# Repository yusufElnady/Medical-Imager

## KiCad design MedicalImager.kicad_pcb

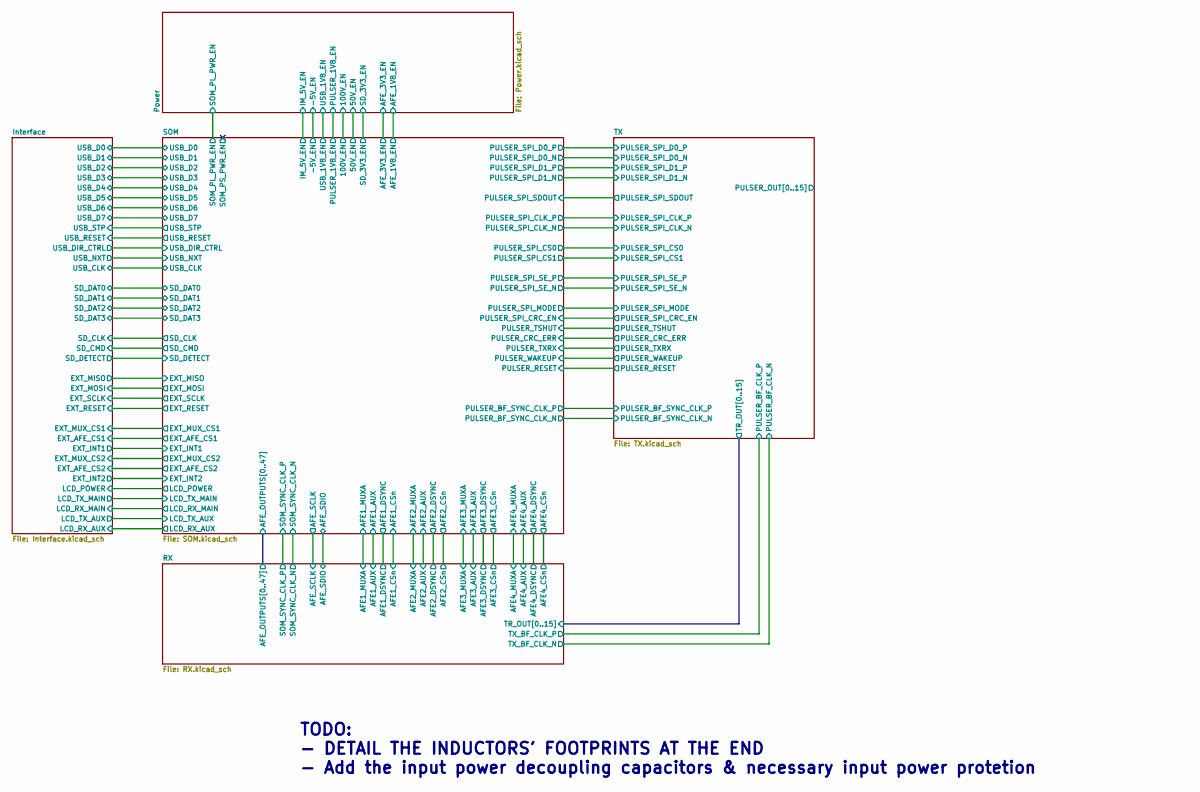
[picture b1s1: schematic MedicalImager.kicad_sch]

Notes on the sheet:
TODO: - DETAIL THE INDUCTORS' FOOTPRINTS AT THE END - Add the input power decoupling capacitors & necessary input power protetion

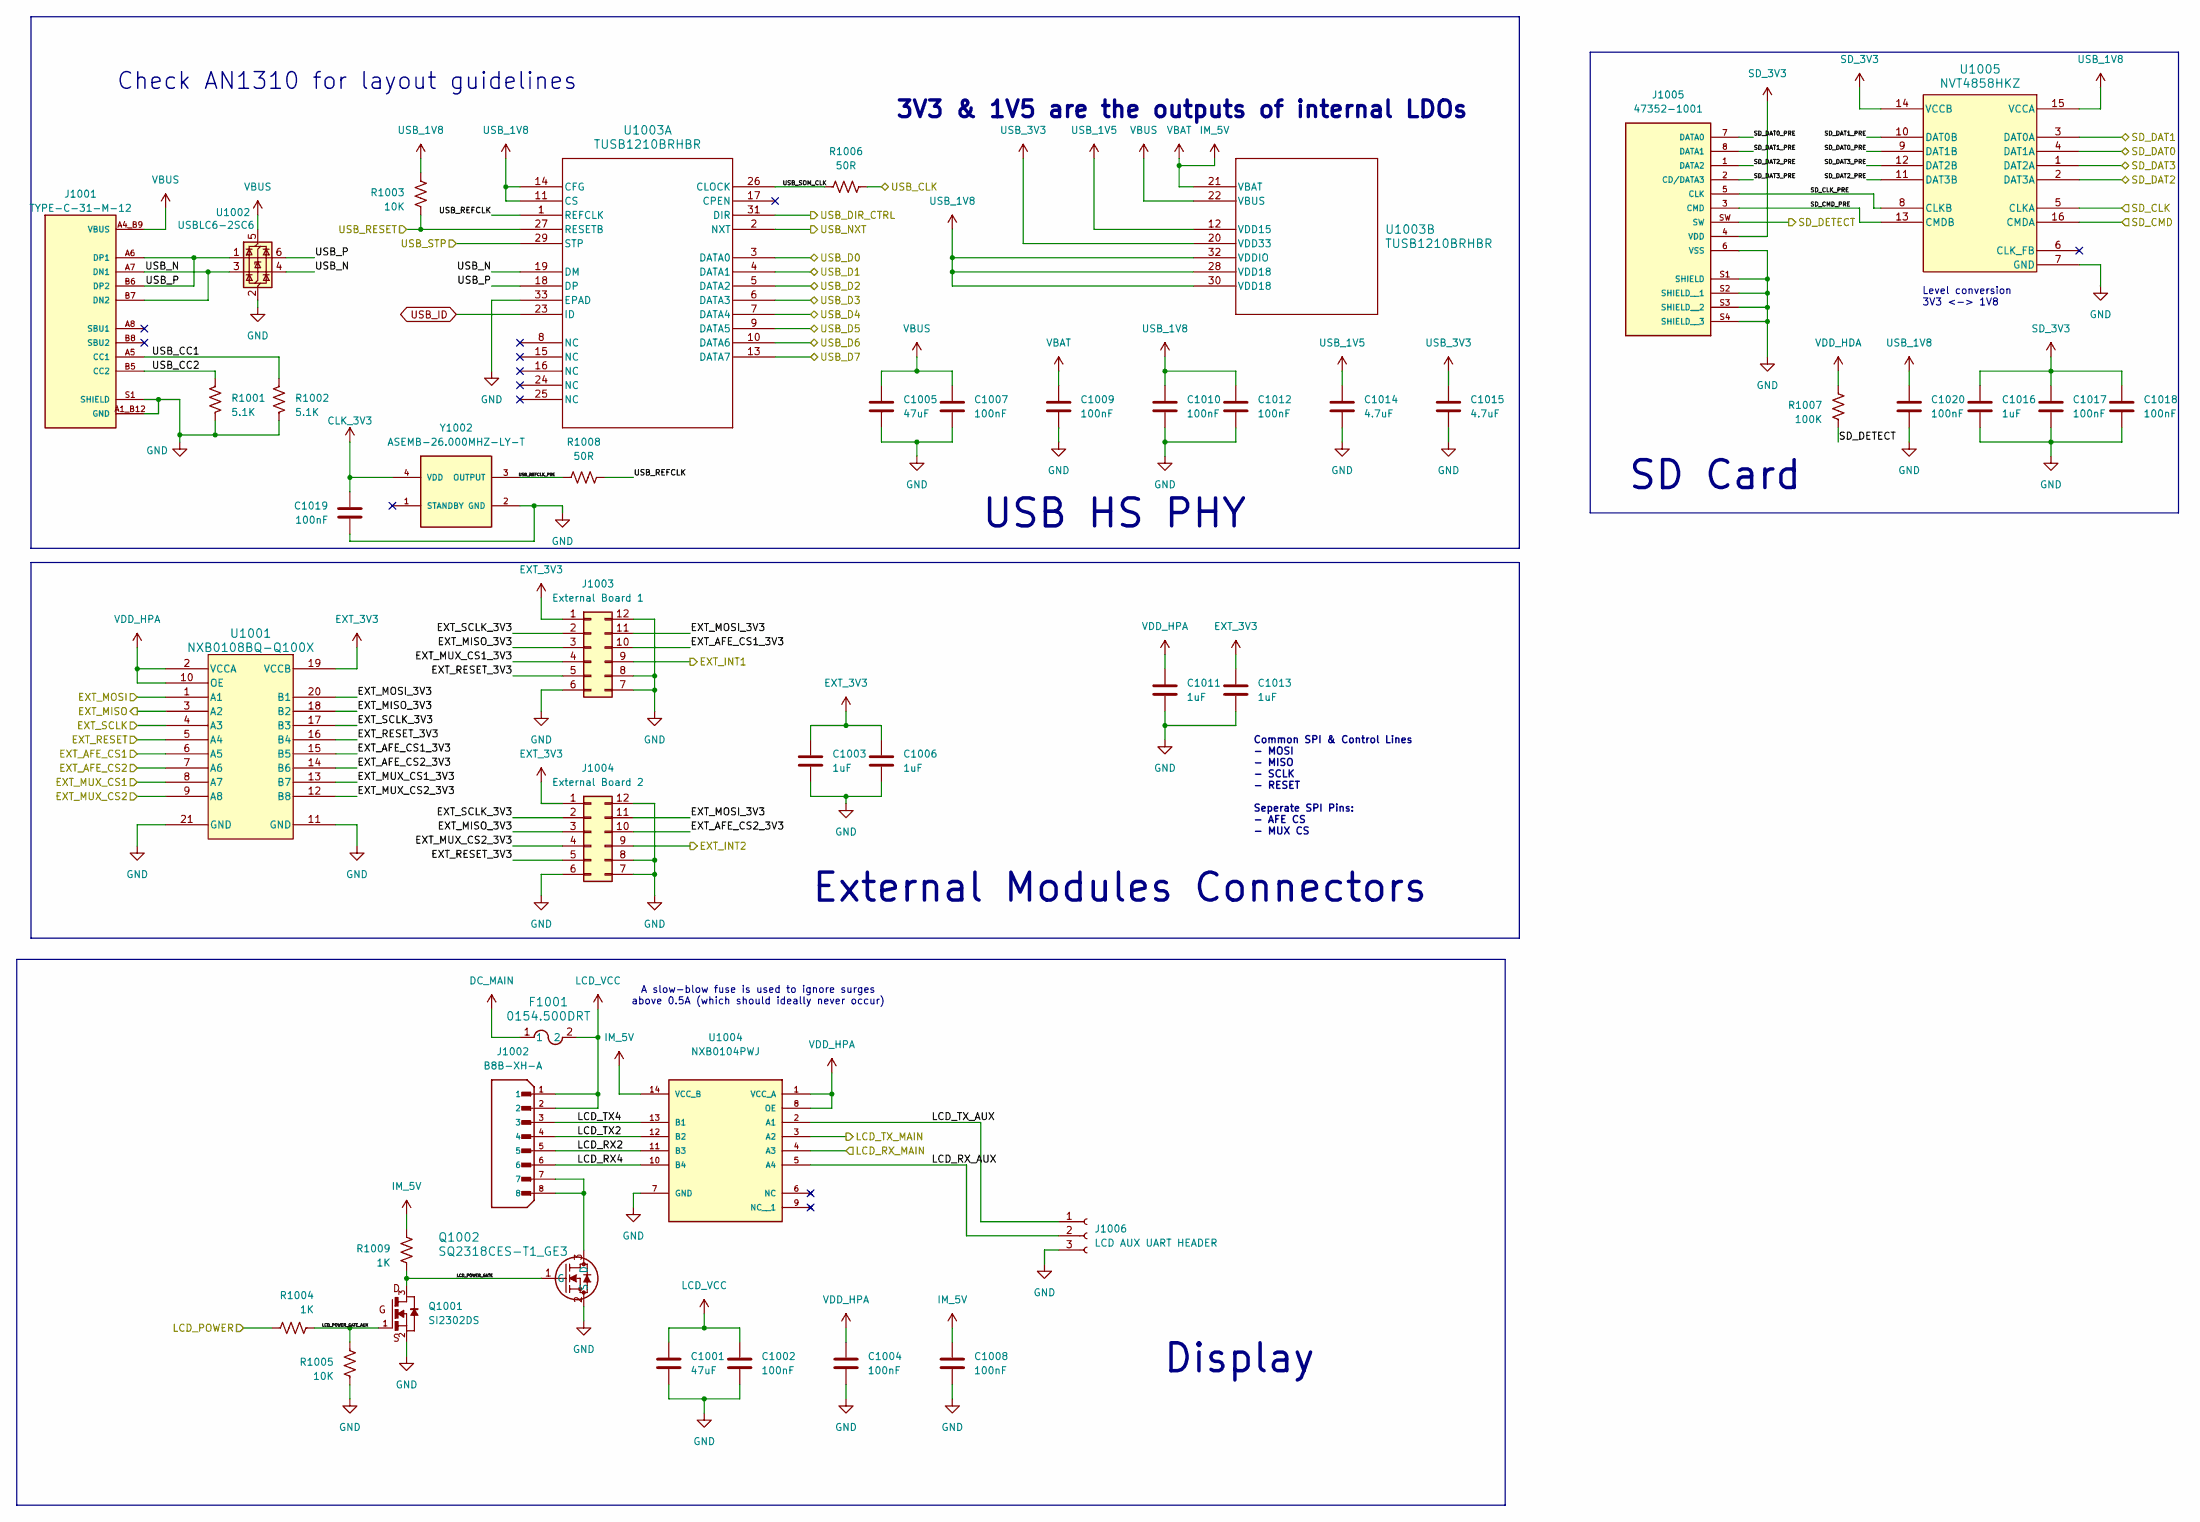
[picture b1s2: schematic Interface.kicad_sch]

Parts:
C1001, C1005: 47uF; C_0805_2012Metric
C1002: 100nF; C_0805_2012Metric
C1003, C1006, C1011, C1013, C1016: 1uF; C_0402_1005Metric
C1004, C1007, C1008, C1009, C1010, C1012, C1017, C1018, C1019, C1020: 100nF; C_0402_1005Metric
C1014, C1015: 4.7uF; C_0402_1005Metric
F1001: 0154.500DRT; 0154Series_LTF
J1001: TYPE-C-31-M-12; HRO_TYPE-C-31-M-12; PARTREV 2020.12.08
J1002: B8B-XH-A; JST_B8B-XH-A; PARTREV 7/4/21
J1003: External Board 1; PinHeader_2x06_P2.54mm_Vertical
J1004: External Board 2; PinHeader_2x06_P2.54mm_Vertical
J1005: 47352-1001; MOLEX_47352-1001; PARTREV K
J1006: LCD AUX UART HEADER; PinSocket_1x03_P2.54mm_Vertical
Q1001: SI2302DS; SOT23-3_TO-236AB
Q1002: SQ2318CES-T1_GE3; NMOSGSD_SOT-23_TO-236_VIS
R1001, R1002: 5.1K; R_0402_1005Metric
R1003, R1005: 10K; R_0402_1005Metric
R1004, R1009: 1K; R_0402_1005Metric
R1006, R1008: 50R; R_0402_1005Metric
R1007: 100K; R_0402_1005Metric
U1001: NXB0108BQ-Q100X; DHVQFN20_SOT764-1_NEX
U1002: USBLC6-2SC6; SOT-23-6
U1003: TUSB1210BRHBR; RHB32_3P45X3P45
U1004: NXB0104PWJ; SOP65P640X120-14N; PARTREV 4
U1005: NVT4858HKZ; NVT4858_NXP
Y1002: ASEMB-26.000MHZ-LY-T; XTAL_ASEMB-26.000MHZ-LY-T; PARTREV 1.4.2021

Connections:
/Interface/EXT_AFE_CS1: U1001.6 (A5); also elsewhere on the board
/Interface/EXT_AFE_CS1_3V3: J1003.10, U1001.15 (B5)
/Interface/EXT_AFE_CS2: U1001.7 (A6); also elsewhere on the board
/Interface/EXT_AFE_CS2_3V3: J1004.10, U1001.14 (B6)
/Interface/EXT_INT1: J1003.9; also elsewhere on the board
/Interface/EXT_INT2: J1004.9; also elsewhere on the board
/Interface/EXT_MISO: U1001.3 (A2); also elsewhere on the board
/Interface/EXT_MISO_3V3: J1003.3, J1004.3, U1001.18 (B2)
/Interface/EXT_MOSI: U1001.1 (A1); also elsewhere on the board
/Interface/EXT_MOSI_3V3: J1003.11, J1004.11, U1001.20 (B1)
/Interface/EXT_MUX_CS1: U1001.8 (A7); also elsewhere on the board
/Interface/EXT_MUX_CS1_3V3: J1003.4, U1001.13 (B7)
/Interface/EXT_MUX_CS2: U1001.9 (A8); also elsewhere on the board
/Interface/EXT_MUX_CS2_3V3: J1004.4, U1001.12 (B8)
/Interface/EXT_RESET: U1001.5 (A4); also elsewhere on the board
/Interface/EXT_RESET_3V3: J1003.5, J1004.5, U1001.16 (B4)
/Interface/EXT_SCLK: U1001.4 (A3); also elsewhere on the board
/Interface/EXT_SCLK_3V3: J1003.2, J1004.2, U1001.17 (B3)
/Interface/LCD_POWER: R1004.2; also elsewhere on the board
/Interface/LCD_POWER_GATE: Q1001.3, Q1002.1 (G), R1009.2
/Interface/LCD_POWER_GATE_AUX: Q1001.1, R1004.1, R1005.1
/Interface/LCD_RX2: J1002.5, U1004.11 (B3)
/Interface/LCD_RX4: J1002.6, U1004.10 (B4)
/Interface/LCD_RX_AUX: J1006.2, U1004.5 (A4)
/Interface/LCD_RX_MAIN: U1004.4 (A3); also elsewhere on the board
/Interface/LCD_TX2: J1002.4, U1004.12 (B2)
/Interface/LCD_TX4: J1002.3, U1004.13 (B1)
/Interface/LCD_TX_AUX: J1006.1, U1004.2 (A1)
/Interface/LCD_TX_MAIN: U1004.3 (A2); also elsewhere on the board
/Interface/SD_CLK: U1005.5 (CLKA); also elsewhere on the board
/Interface/SD_CLK_PRE: J1005.5 (CLK), U1005.8 (CLKB)
/Interface/SD_CMD: U1005.16 (CMDA); also elsewhere on the board
/Interface/SD_CMD_PRE: J1005.3 (CMD), U1005.13 (CMDB)
/Interface/SD_DAT0: U1005.4 (DAT1A); also elsewhere on the board
/Interface/SD_DAT0_PRE: J1005.7 (DATA0), U1005.9 (DAT1B)
/Interface/SD_DAT1: U1005.3 (DAT0A); also elsewhere on the board
/Interface/SD_DAT1_PRE: J1005.8 (DATA1), U1005.10 (DAT0B)
/Interface/SD_DAT2: U1005.2 (DAT3A); also elsewhere on the board
/Interface/SD_DAT2_PRE: J1005.1 (DATA2), U1005.11 (DAT3B)
/Interface/SD_DAT3: U1005.1 (DAT2A); also elsewhere on the board
/Interface/SD_DAT3_PRE: J1005.2 (CD/DATA3), U1005.12 (DAT2B)
/Interface/SD_DETECT: J1005.SW, R1007.2; also elsewhere on the board
/Interface/USB_CC1: J1001.A5 (CC1), R1002.1
/Interface/USB_CC2: J1001.B5 (CC2), R1001.1
/Interface/USB_CLK: R1006.1; also elsewhere on the board
/Interface/USB_D0: U1003.3 (DATA0); also elsewhere on the board
/Interface/USB_D1: U1003.4 (DATA1); also elsewhere on the board
/Interface/USB_D2: U1003.5 (DATA2); also elsewhere on the board
/Interface/USB_D3: U1003.6 (DATA3); also elsewhere on the board
/Interface/USB_D4: U1003.7 (DATA4); also elsewhere on the board
/Interface/USB_D5: U1003.9 (DATA5); also elsewhere on the board
/Interface/USB_D6: U1003.10 (DATA6); also elsewhere on the board
/Interface/USB_D7: U1003.13 (DATA7); also elsewhere on the board
/Interface/USB_DIR_CTRL: U1003.31 (DIR); also elsewhere on the board
/Interface/USB_N: J1001.A7 (DN1), J1001.B7 (DN2), U1002.3 (I/O2), U1002.4 (I/O2), U1003.19 (DM)
/Interface/USB_NXT: U1003.2 (NXT); also elsewhere on the board
/Interface/USB_P: J1001.A6 (DP1), J1001.B6 (DP2), U1002.1 (I/O1), U1002.6 (I/O1), U1003.18 (DP)
/Interface/USB_REFCLK: R1008.1, U1003.1 (REFCLK)
/Interface/USB_REFCLK_PRE: R1008.2, Y1002.3 (OUTPUT)
/Interface/USB_RESET: R1003.2, U1003.27 (RESETB); also elsewhere on the board
/Interface/USB_SOM_CLK: R1006.2, U1003.26 (CLOCK)
/Interface/USB_STP: U1003.29 (STP); also elsewhere on the board
CLK_3V3: C1019.2, Y1002.4 (VDD); also elsewhere on the board
DC_MAIN: F1001.1; also elsewhere on the board
EXT_3V3: C1003.1, C1006.1, C1013.1, J1003.1, J1004.1, U1001.19 (VCCB); also elsewhere on the board
GND: C1001.2, C1002.1, C1003.2, C1004.1, C1005.2, C1006.2, C1007.1, C1008.1, C1009.1, C1010.1, C1011.2, C1012.1, C1013.2, C1014.1, C1015.1, C1016.2, C1017.2, C1018.2, C1019.1, C1020.2, J1001.A1_B12 (GND), J1001.B1_A12 (GND), J1001.S1 (SHIELD), J1001.S2 (SHIELD), J1001.S3 (SHIELD), J1001.S4 (SHIELD), J1003.6, J1003.7, J1003.8, J1003.12, J1004.6, J1004.7, J1004.8, J1004.12, J1005.6 (VSS), J1005.S1 (SHIELD), J1005.S2 (SHIELD__1), J1005.S3 (SHIELD__2), J1005.S4 (SHIELD__3), J1006.3, Q1001.2, Q1002.2 (S), R1001.2, R1002.2, R1005.2, U1001.11 (GND), U1001.21 (GND), U1002.2 (GND), U1003.33 (EPAD), U1004.7 (GND), U1005.7 (GND), Y1002.2 (GND); also elsewhere on the board
IM_5V: C1008.2, C1009.2, R1009.1, U1003.21 (VBAT), U1004.14 (VCC_B); also elsewhere on the board
LCD_VCC: C1001.1, C1002.2, F1001.2, J1002.1, J1002.2
unnamed: J1002.7, J1002.8, Q1002.3 (D)
SD_3V3: C1016.1, C1017.1, C1018.1, J1005.4 (VDD), U1005.14 (VCCB); also elsewhere on the board
USB_1V5: C1014.2, U1003.12 (VDD15)
USB_1V8: C1010.2, C1012.2, C1020.1, R1003.1, U1003.11 (CS), U1003.14 (CFG), U1003.28 (VDD18), U1003.30 (VDD18), U1003.32 (VDDIO), U1005.15 (VCCA); also elsewhere on the board
USB_3V3: C1015.2, U1003.20 (VDD33)
USB_ID: U1003.23 (ID)
VBUS: C1005.1, C1007.2, J1001.A4_B9 (VBUS), J1001.B4_A9 (VBUS), U1002.5 (VBUS), U1003.22 (VBUS)
VDD_HDA: R1007.1; also elsewhere on the board
VDD_HPA: C1004.2, C1011.1, U1001.2 (VCCA), U1001.10 (OE), U1004.1 (VCC_A), U1004.8 (OE); also elsewhere on the board

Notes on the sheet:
Level conversion 3V3 <-> 1V8
USB HS PHY
3V3 & 1V5 are the outputs of internal LDOs
SD Card
Display
Check AN1310 for layout guidelines
External Modules Connectors
A slow-blow fuse is used to ignore surges above 0.5A (which should ideally never occur)
Common SPI & Control Lines - MOSI - MISO - SCLK - RESET Seperate SPI Pins: - AFE CS - MUX CS

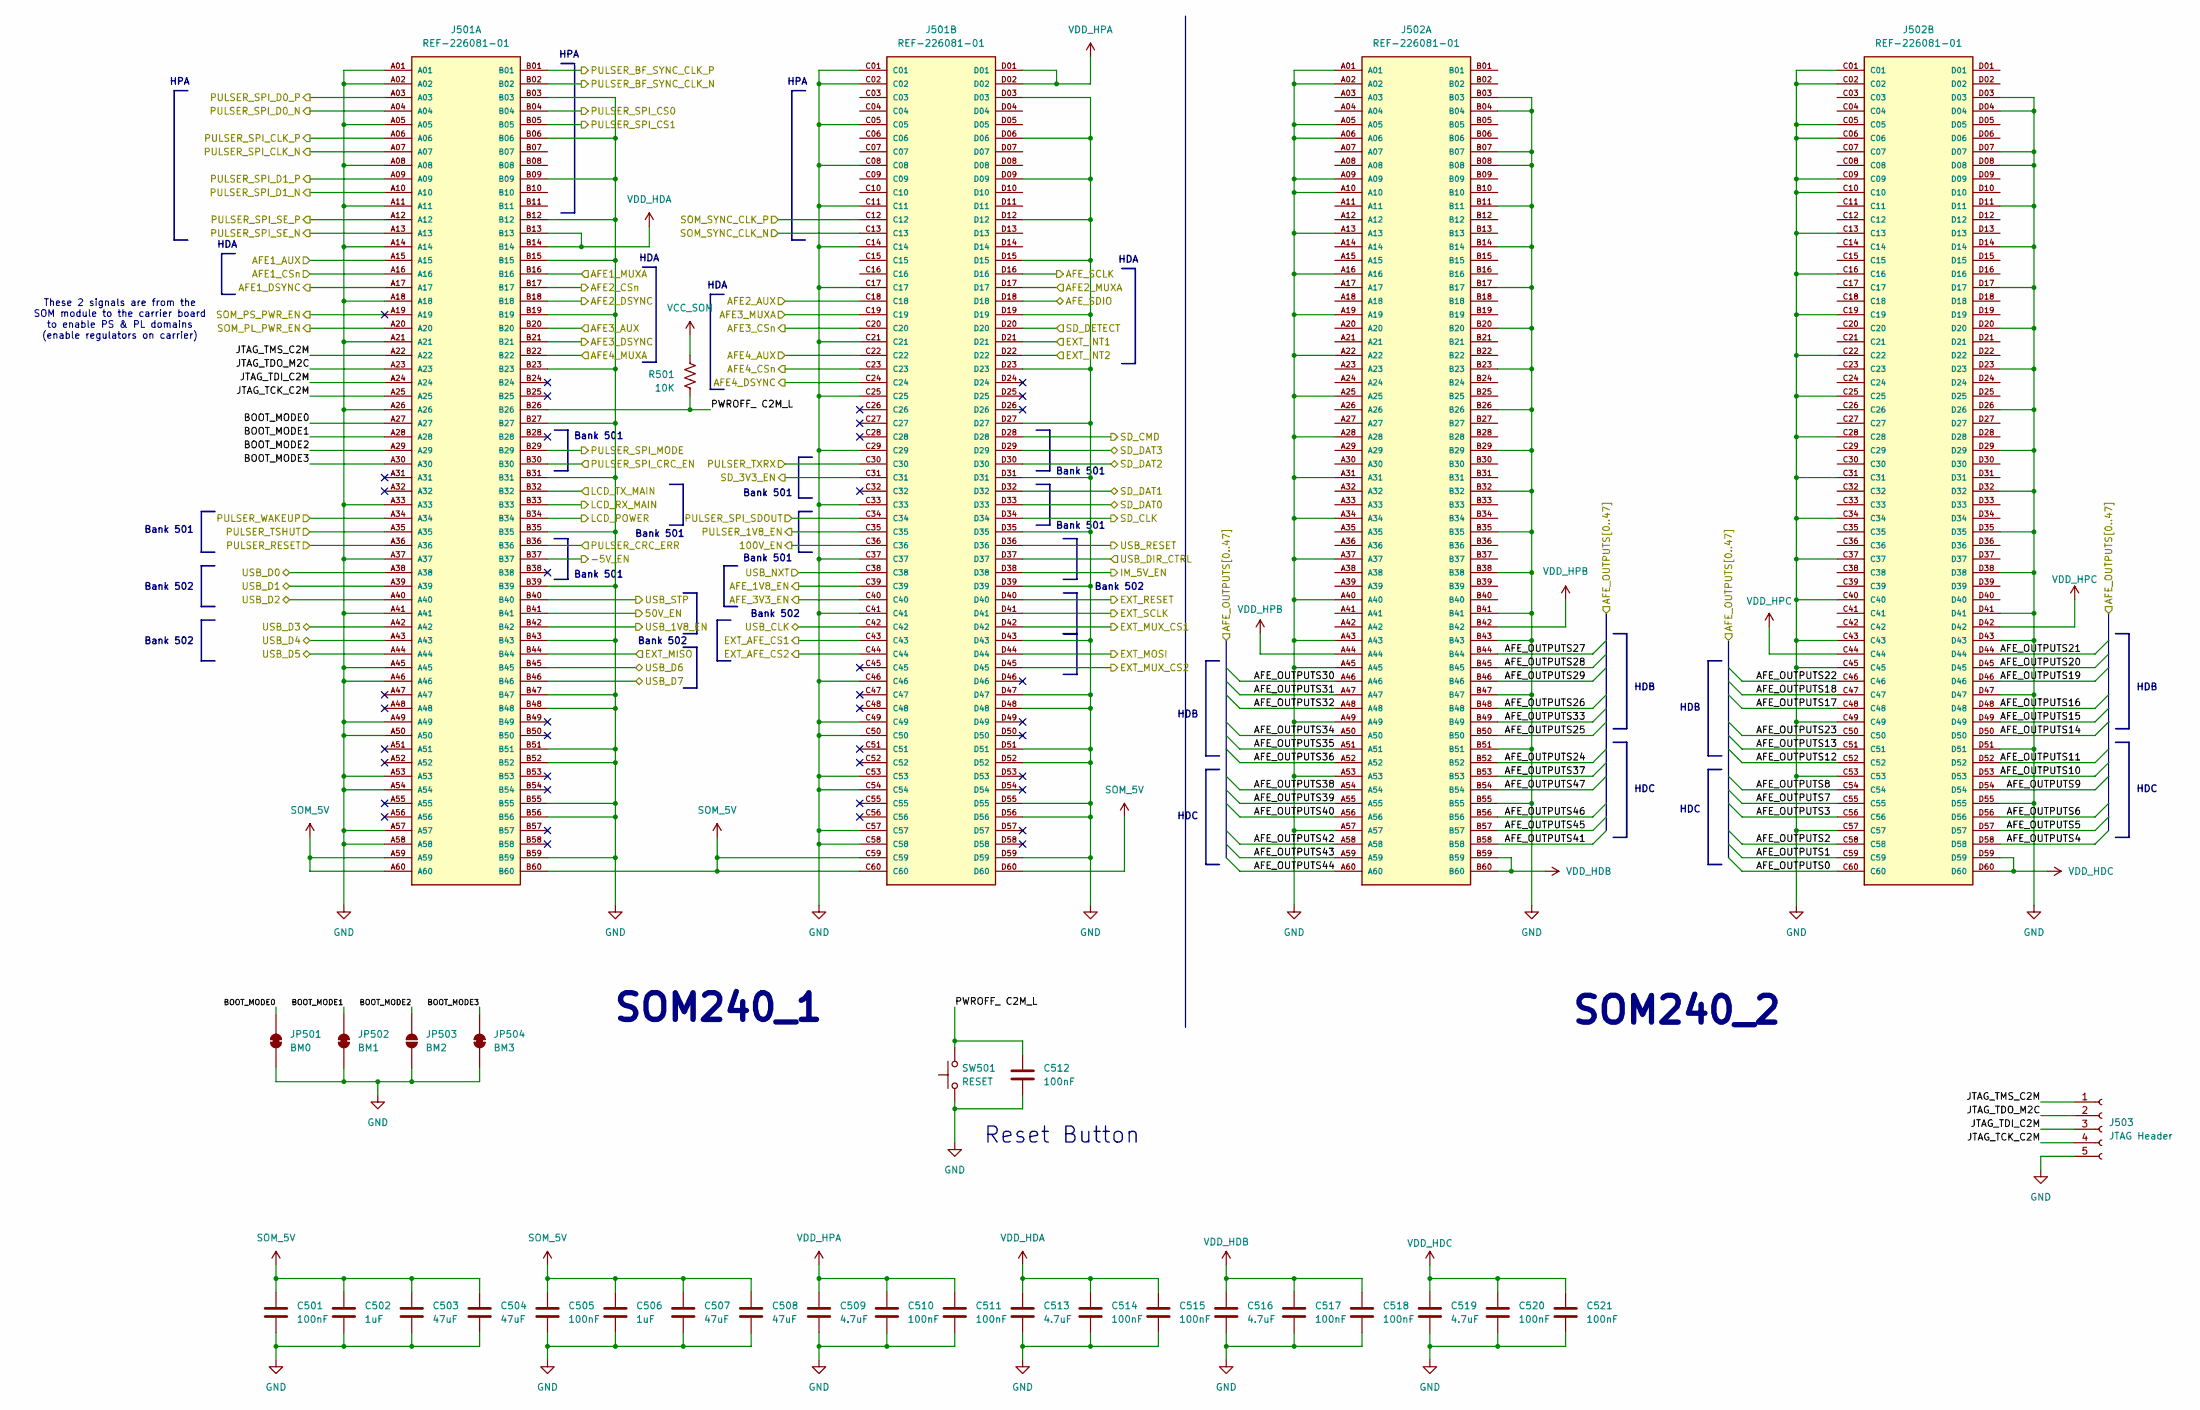
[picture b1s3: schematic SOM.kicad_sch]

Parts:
C501, C505, C510, C511, C512, C514, C515, C517, C518, C520, C521: 100nF; C_0402_1005Metric
C502, C506: 1uF; C_0402_1005Metric
C503, C504, C507, C508: 47uF; C_0805_2012Metric
C509, C513, C516, C519: 4.7uF; C_0805_2012Metric
J501, J502: REF-226081-01; SAMTEC_REF-226081-01; PARTREV C
J503: JTAG Header; PinSocket_1x05_P2.54mm_Vertical
JP501: BM0; SolderJumper-2_P1.3mm_Bridged_RoundedPad1.0x1.5mm
JP502: BM1; SolderJumper-2_P1.3mm_Bridged_RoundedPad1.0x1.5mm
JP503: BM2; SolderJumper-2_P1.3mm_Open_TrianglePad1.0x1.5mm
JP504: BM3; SolderJumper-2_P1.3mm_Bridged_RoundedPad1.0x1.5mm
R501: 10K; R_0402_1005Metric
SW501: RESET; SW_Push_SPST_NO_Alps_SKRK

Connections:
/Interface/EXT_AFE_CS1: J501.C43; also elsewhere on the board
/Interface/EXT_AFE_CS2: J501.C44; also elsewhere on the board
/Interface/EXT_INT1: J501.D21; also elsewhere on the board
/Interface/EXT_INT2: J501.D22; also elsewhere on the board
/Interface/EXT_MISO: J501.B44; also elsewhere on the board
/Interface/EXT_MOSI: J501.D44; also elsewhere on the board
/Interface/EXT_MUX_CS1: J501.D42; also elsewhere on the board
/Interface/EXT_MUX_CS2: J501.D45; also elsewhere on the board
/Interface/EXT_RESET: J501.D40; also elsewhere on the board
/Interface/EXT_SCLK: J501.D41; also elsewhere on the board
/Interface/LCD_POWER: J501.B34; also elsewhere on the board
/Interface/LCD_RX_MAIN: J501.B33; also elsewhere on the board
/Interface/LCD_TX_MAIN: J501.B32; also elsewhere on the board
/Interface/SD_CLK: J501.D34; also elsewhere on the board
/Interface/SD_CMD: J501.D28; also elsewhere on the board
/Interface/SD_DAT0: J501.D33; also elsewhere on the board
/Interface/SD_DAT1: J501.D32; also elsewhere on the board
/Interface/SD_DAT2: J501.D30; also elsewhere on the board
/Interface/SD_DAT3: J501.D29; also elsewhere on the board
/Interface/SD_DETECT: J501.D20; also elsewhere on the board
/Interface/USB_CLK: J501.C42; also elsewhere on the board
/Interface/USB_D0: J501.A38; also elsewhere on the board
/Interface/USB_D1: J501.A39; also elsewhere on the board
/Interface/USB_D2: J501.A40; also elsewhere on the board
/Interface/USB_D3: J501.A42; also elsewhere on the board
/Interface/USB_D4: J501.A43; also elsewhere on the board
/Interface/USB_D5: J501.A44; also elsewhere on the board
/Interface/USB_D6: J501.B45; also elsewhere on the board
/Interface/USB_D7: J501.B46; also elsewhere on the board
/Interface/USB_DIR_CTRL: J501.D37; also elsewhere on the board
/Interface/USB_NXT: J501.C38; also elsewhere on the board
/Interface/USB_RESET: J501.D36; also elsewhere on the board
/Interface/USB_STP: J501.B40; also elsewhere on the board
/Power/50V_EN: J501.B41; also elsewhere on the board
/Power/100V_EN: J501.C36; also elsewhere on the board
/Power/-5V_EN: J501.B37; also elsewhere on the board
/Power/IM_5V_EN: J501.D38; also elsewhere on the board
/Power/PULSER_1V8_EN: J501.C35; also elsewhere on the board
/Power/SD_3V3_EN: J501.C31; also elsewhere on the board
/Power/SOM_PL_PWR_EN: J501.A20; also elsewhere on the board
/Power/USB_1V8_EN: J501.B42; also elsewhere on the board
/RX/AFE1_AUX: J501.A15; also elsewhere on the board
/RX/AFE1_CSn: J501.A16; also elsewhere on the board
/RX/AFE1_DSYNC: J501.A17; also elsewhere on the board
/RX/AFE1_MUXA: J501.B16; also elsewhere on the board
/RX/AFE2_AUX: J501.C18; also elsewhere on the board
/RX/AFE2_CSn: J501.B17; also elsewhere on the board
/RX/AFE2_DSYNC: J501.B18; also elsewhere on the board
/RX/AFE2_MUXA: J501.D17; also elsewhere on the board
/RX/AFE3_AUX: J501.B20; also elsewhere on the board
/RX/AFE3_CSn: J501.C20; also elsewhere on the board
/RX/AFE3_DSYNC: J501.B21; also elsewhere on the board
/RX/AFE3_MUXA: J501.C19; also elsewhere on the board
/RX/AFE4_AUX: J501.C22; also elsewhere on the board
/RX/AFE4_CSn: J501.C23; also elsewhere on the board
/RX/AFE4_DSYNC: J501.C24; also elsewhere on the board
/RX/AFE4_MUXA: J501.B22; also elsewhere on the board
/RX/AFE_OUTPUTS0: J502.C60; also elsewhere on the board
/RX/AFE_OUTPUTS1: J502.C59; also elsewhere on the board
/RX/AFE_OUTPUTS2: J502.C58; also elsewhere on the board
/RX/AFE_OUTPUTS3: J502.C56; also elsewhere on the board
/RX/AFE_OUTPUTS4: J502.D58; also elsewhere on the board
/RX/AFE_OUTPUTS5: J502.D57; also elsewhere on the board
/RX/AFE_OUTPUTS6: J502.D56; also elsewhere on the board
/RX/AFE_OUTPUTS7: J502.C55; also elsewhere on the board
/RX/AFE_OUTPUTS8: J502.C54; also elsewhere on the board
/RX/AFE_OUTPUTS9: J502.D54; also elsewhere on the board
/RX/AFE_OUTPUTS10: J502.D53; also elsewhere on the board
/RX/AFE_OUTPUTS11: J502.D52; also elsewhere on the board
/RX/AFE_OUTPUTS12: J502.C52; also elsewhere on the board
/RX/AFE_OUTPUTS13: J502.C51; also elsewhere on the board
/RX/AFE_OUTPUTS14: J502.D50; also elsewhere on the board
/RX/AFE_OUTPUTS15: J502.D49; also elsewhere on the board
/RX/AFE_OUTPUTS16: J502.D48; also elsewhere on the board
/RX/AFE_OUTPUTS17: J502.C48; also elsewhere on the board
/RX/AFE_OUTPUTS18: J502.C47; also elsewhere on the board
/RX/AFE_OUTPUTS19: J502.D46; also elsewhere on the board
/RX/AFE_OUTPUTS20: J502.D45; also elsewhere on the board
/RX/AFE_OUTPUTS21: J502.D44; also elsewhere on the board
/RX/AFE_OUTPUTS22: J502.C46; also elsewhere on the board
/RX/AFE_OUTPUTS23: J502.C50; also elsewhere on the board
/RX/AFE_OUTPUTS24: J502.B52; also elsewhere on the board
/RX/AFE_OUTPUTS25: J502.B50; also elsewhere on the board
/RX/AFE_OUTPUTS26: J502.B48; also elsewhere on the board
/RX/AFE_OUTPUTS27: J502.B44; also elsewhere on the board
/RX/AFE_OUTPUTS28: J502.B45; also elsewhere on the board
/RX/AFE_OUTPUTS29: J502.B46; also elsewhere on the board
/RX/AFE_OUTPUTS30: J502.A46; also elsewhere on the board
/RX/AFE_OUTPUTS31: J502.A47; also elsewhere on the board
/RX/AFE_OUTPUTS32: J502.A48; also elsewhere on the board
/RX/AFE_OUTPUTS33: J502.B49; also elsewhere on the board
/RX/AFE_OUTPUTS34: J502.A50; also elsewhere on the board
/RX/AFE_OUTPUTS35: J502.A51; also elsewhere on the board
/RX/AFE_OUTPUTS36: J502.A52; also elsewhere on the board
/RX/AFE_OUTPUTS37: J502.B53; also elsewhere on the board
/RX/AFE_OUTPUTS38: J502.A54; also elsewhere on the board
/RX/AFE_OUTPUTS39: J502.A55; also elsewhere on the board
/RX/AFE_OUTPUTS40: J502.A56; also elsewhere on the board
/RX/AFE_OUTPUTS41: J502.B58; also elsewhere on the board
/RX/AFE_OUTPUTS42: J502.A58; also elsewhere on the board
/RX/AFE_OUTPUTS43: J502.A59; also elsewhere on the board
/RX/AFE_OUTPUTS44: J502.A60; also elsewhere on the board
/RX/AFE_OUTPUTS45: J502.B57; also elsewhere on the board
/RX/AFE_OUTPUTS46: J502.B56; also elsewhere on the board
/RX/AFE_OUTPUTS47: J502.B54; also elsewhere on the board
/RX/AFE_SCLK: J501.D16; also elsewhere on the board
/RX/AFE_SDIO: J501.D18; also elsewhere on the board
/RX/SOM_SYNC_CLK_N: J501.C13; also elsewhere on the board
/RX/SOM_SYNC_CLK_P: J501.C12; also elsewhere on the board
/SOM/AFE_1V8_EN: J501.C39
/SOM/AFE_3V3_EN: J501.C40
/SOM/BOOT_MODE0: J501.A27, JP501.2 (B)
/SOM/BOOT_MODE1: J501.A28, JP502.2 (B)
/SOM/BOOT_MODE2: J501.A29, JP503.2 (B)
/SOM/BOOT_MODE3: J501.A30, JP504.2 (B)
/SOM/JTAG_TCK_C2M: J501.A25, J503.4
/SOM/JTAG_TDI_C2M: J501.A24, J503.3
/SOM/JTAG_TDO_M2C: J501.A23, J503.2
/SOM/JTAG_TMS_C2M: J501.A22, J503.1
/SOM/PULSER_BF_SYNC_CLK_N: J501.B02; also elsewhere on the board
/SOM/PULSER_BF_SYNC_CLK_P: J501.B01; also elsewhere on the board
/SOM/PULSER_RESET: J501.A36; also elsewhere on the board
/SOM/PULSER_SPI_CLK_N: J501.A07; also elsewhere on the board
/SOM/PULSER_SPI_CLK_P: J501.A06; also elsewhere on the board
/SOM/PULSER_SPI_CRC_EN: J501.B30; also elsewhere on the board
/SOM/PULSER_SPI_CS0: J501.B04; also elsewhere on the board
/SOM/PULSER_SPI_CS1: J501.B05; also elsewhere on the board
/SOM/PULSER_SPI_D0_N: J501.A04; also elsewhere on the board
/SOM/PULSER_SPI_D0_P: J501.A03; also elsewhere on the board
/SOM/PULSER_SPI_D1_N: J501.A10; also elsewhere on the board
/SOM/PULSER_SPI_D1_P: J501.A09; also elsewhere on the board
/SOM/PULSER_SPI_MODE: J501.B29; also elsewhere on the board
/SOM/PULSER_SPI_SDOUT: J501.C34; also elsewhere on the board
/SOM/PULSER_SPI_SE_N: J501.A13; also elsewhere on the board
/SOM/PULSER_SPI_SE_P: J501.A12; also elsewhere on the board
/SOM/PULSER_WAKEUP: J501.A34; also elsewhere on the board
/SOM/PWROFF_ C2M_L: C512.1, J501.B26, R501.2, SW501.2
/SOM/SOM_PS_PWR_EN: J501.A19
/TX/PULSER_CRC_ERR: J501.B36; also elsewhere on the board
/TX/PULSER_TSHUT: J501.A35; also elsewhere on the board
/TX/PULSER_TXRX: J501.C30; also elsewhere on the board
GND: C501.2, C502.2, C503.2, C504.2, C505.2, C506.2, C507.2, C508.2, C509.2, C510.2, C511.2, C512.2, C513.2, C514.2, C515.2, C516.2, C517.2, C518.2, C519.2, C520.2, C521.2, J501.A01, J501.A02, J501.A05, J501.A08, J501.A11, J501.A14, J501.A18, J501.A21, J501.A26, J501.A33, J501.A37, J501.A41, J501.A45, J501.A46, J501.A49, J501.A50, J501.A53, J501.A54, J501.A57, J501.A58, J501.B03, J501.B06, J501.B09, J501.B12, J501.B15, J501.B19, J501.B23, J501.B27, J501.B31, J501.B35, J501.B39, J501.B43, J501.B47, J501.B48, J501.B51, J501.B52, J501.B55, J501.B56, J501.B59, J501.C01, J501.C02, J501.C05, J501.C08, J501.C11, J501.C14, J501.C17, J501.C21, J501.C25, J501.C29, J501.C33, J501.C37, J501.C41, J501.C46, J501.C49, J501.C50, J501.C53, J501.C54, J501.C57, J501.C58, J501.D03, J501.D06, J501.D09, J501.D12, J501.D15, J501.D19, J501.D23, J501.D27, J501.D31, J501.D35, J501.D39, J501.D43, J501.D47, J501.D48, J501.D51, J501.D52, J501.D55, J501.D56, J501.D59, J502.A01, J502.A02, J502.A05, J502.A06, J502.A09, J502.A10, J502.A13, J502.A16, J502.A19, J502.A22, J502.A25, J502.A28, J502.A31, J502.A34, J502.A37, J502.A40, J502.A43, J502.A45, J502.A49, J502.A53, J502.A57, J502.B03, J502.B04, J502.B07, J502.B08, J502.B11, J502.B14, J502.B17, J502.B20, J502.B23, J502.B26, J502.B29, J502.B32, J502.B35, J502.B38, J502.B41, J502.B43, J502.B47, J502.B51, J502.B55, J502.C01, J502.C02, J502.C05, J502.C06, J502.C09, J502.C10, J502.C13, J502.C16, J502.C19, J502.C22, J502.C25, J502.C28, J502.C31, J502.C34, J502.C37, J502.C40, J502.C43, J502.C45, J502.C49, J502.C53, J502.C57, J502.D03, J502.D04, J502.D07, J502.D08, J502.D11, J502.D14, J502.D17, J502.D20, J502.D23, J502.D26, J502.D29, J502.D32, J502.D35, J502.D38, J502.D41, J502.D43, J502.D47, J502.D51, J502.D55, J503.5, JP501.1 (A), JP502.1 (A), JP503.1 (A), JP504.1 (A), SW501.1; also elsewhere on the board
SOM_5V: C501.1, C502.1, C503.1, C504.1, C505.1, C506.1, C507.1, C508.1, J501.A59, J501.A60, J501.B60, J501.C59, J501.C60, J501.D60; also elsewhere on the board
VCC_SOM: R501.1
VDD_HDA: C513.1, C514.1, C515.1, J501.B13, J501.B14; also elsewhere on the board
VDD_HDB: C516.1, C517.1, C518.1, C519.1, C520.1, C521.1, J502.B59, J502.B60, J502.D59, J502.D60; also elsewhere on the board
VDD_HPA: C509.1, C510.1, C511.1, J501.D01, J501.D02; also elsewhere on the board
VDD_HPB: J502.A44, J502.B42
VDD_HPC: J502.C44, J502.D42

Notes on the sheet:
HDA
Bank 501
SOM240_2
HDB
HDC
Bank 502
HPA
SOM240_1
These 2 signals are from the SOM module to the carrier board to enable PS & PL domains (enable regulators on carrier)
Reset Button
